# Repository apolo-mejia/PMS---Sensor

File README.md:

# PMS_Sensor
Power manage System for Microcontrolles ans sensors, in the scope of Syracuza proyect. 
Features:
- Automatic connetion/disconnection, from Li-ION battery protection,
- Automatic disconnection a battery when a external alimentation is provided,
- Compatible with Energy Harvest, <br>

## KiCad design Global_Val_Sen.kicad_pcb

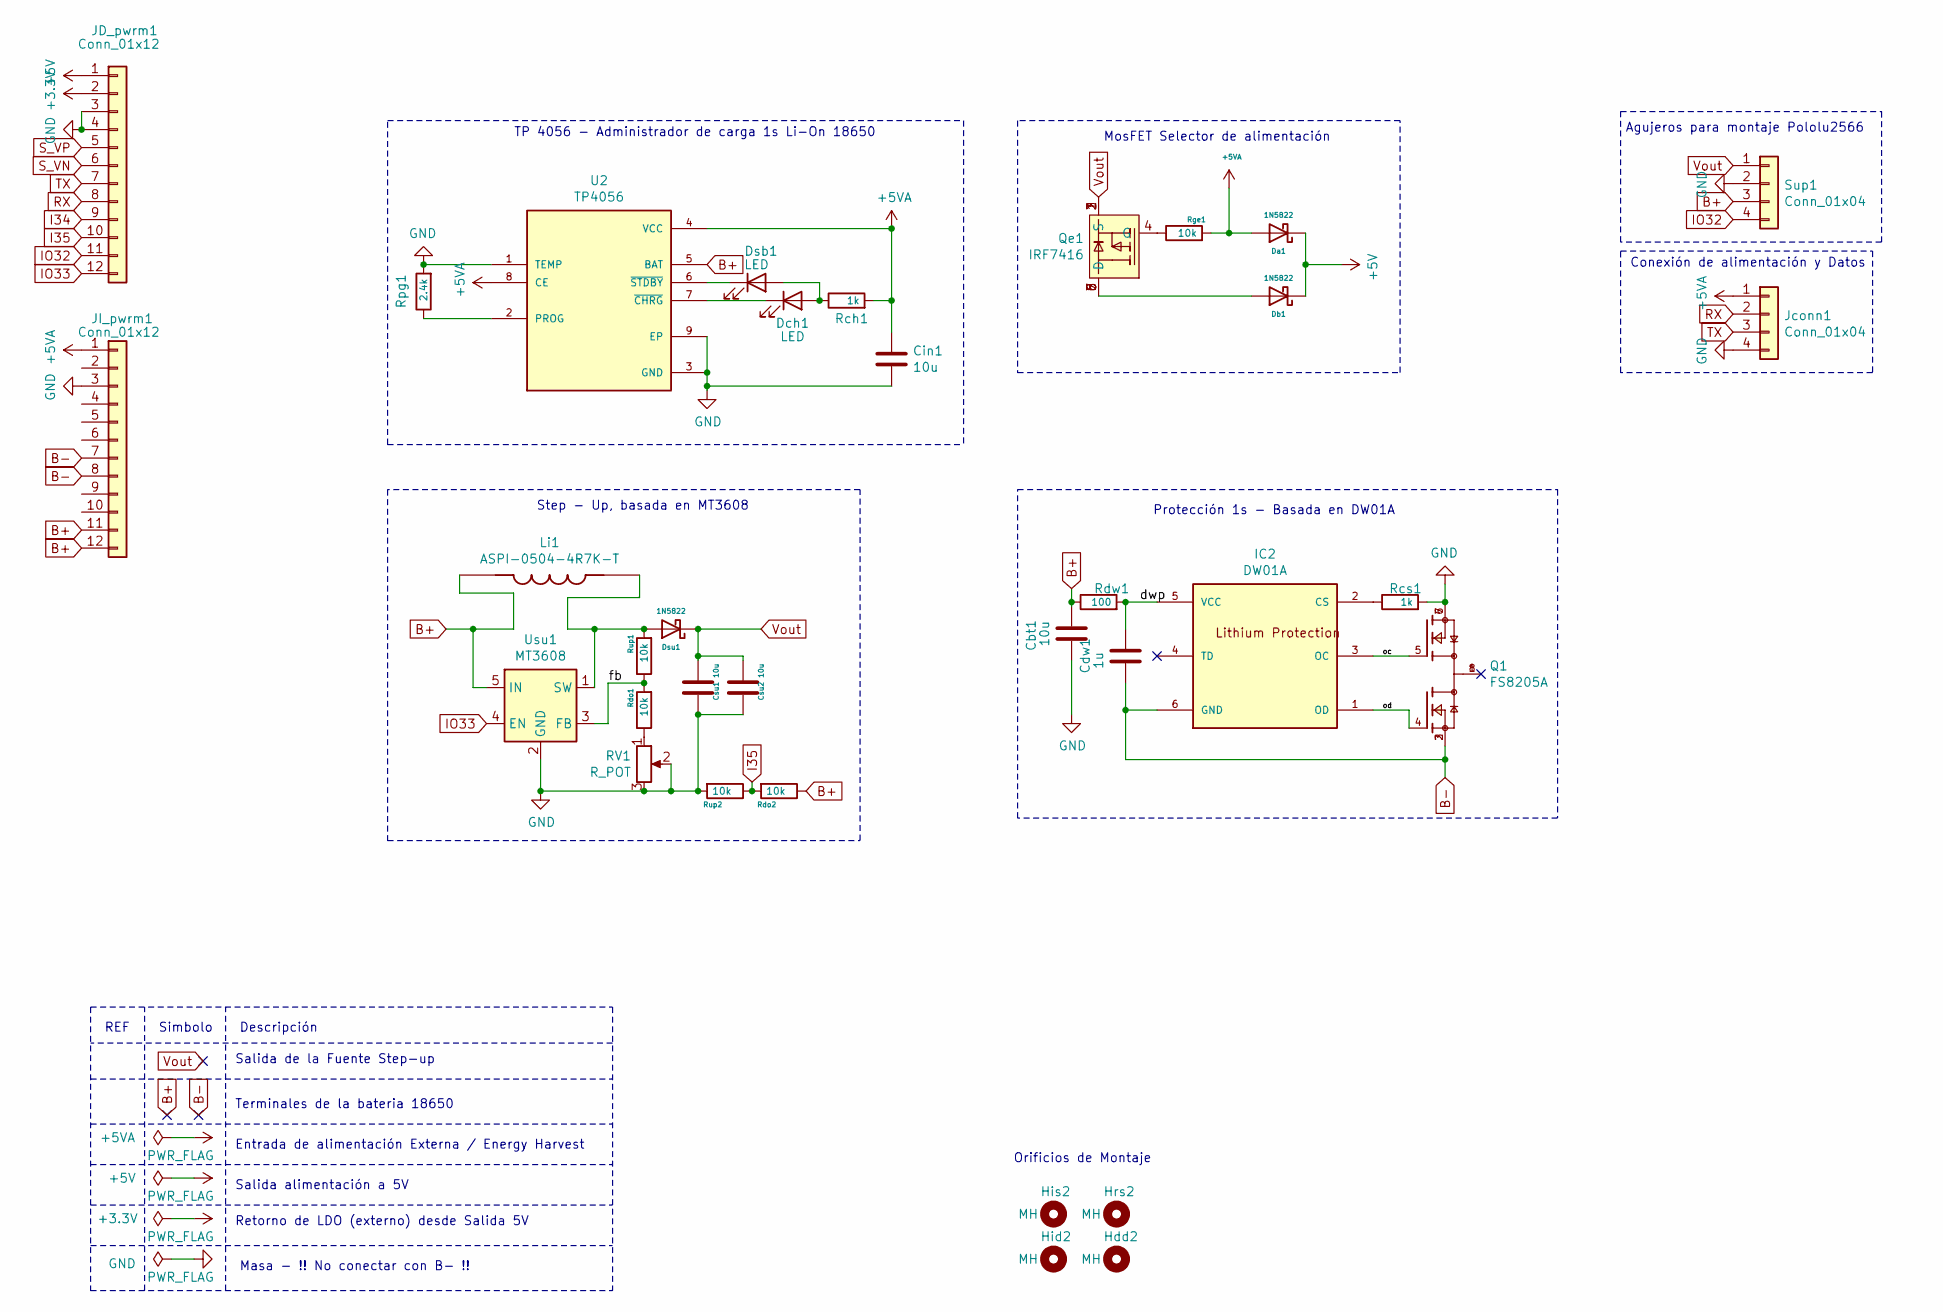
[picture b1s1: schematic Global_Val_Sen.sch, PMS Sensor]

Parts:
Cbt1: 10u; CP_EIA-3216-10_Kemet-I_Pad1.58x1.35mm_HandSolder
Cdw1: 1u; CP_EIA-3216-10_Kemet-I_Pad1.58x1.35mm_HandSolder
Cin1: 10u; CP_EIA-3216-10_Kemet-I_Pad1.58x1.35mm_HandSolder
Csu1, Csu2: 10u; CP_EIA-3216-10_Kemet-I_Pad1.58x1.35mm_HandSolder
Da1: 1N5822; D_SMA
Db1: 1N5822; D_SMA
Dch1: LED; LED_1206_3216Metric_Castellated
Dsb1: LED; LED_1206_3216Metric_Castellated
Dsu1: 1N5822; D_SMA
Hdd2: MH; MountingHole_2.2mm_M2_DIN965
Hid2: MH; MountingHole_2.2mm_M2_DIN965
His2: MH; MountingHole_2.2mm_M2_DIN965
Hrs2: MH; MountingHole_2.2mm_M2_DIN965
IC2: DW01A; SOT-23-6_Handsoldering
JD_pwrm1: Conn_01x12; PinSocket_1x12_P2.00mm_Vertical
JI_pwrm1: Conn_01x12; PinSocket_1x12_P2.00mm_Vertical
Jconn1: Conn_01x04; PinHeader_1x04_P2.00mm_Vertical
Li1: ASPI-0504-4R7K-T; IND_ASPI-0504-4R7K-T; PARTREV 06.24.13
Q1: FS8205A; SOP65P640X120-8N; PARTREV 1.7
Qe1: IRF7416; SO-8_3.9x4.9mm_P1.27mm
RV1: R_POT; Potentiometer_Bourns_TC33X_Vertical
Rch1: 1k; R_1206_3216Metric_Pad1.30x1.75mm_HandSolder
Rcs1: 1k; R_1206_3216Metric_Pad1.30x1.75mm_HandSolder
Rdo1, Rdo2: 10k; R_1206_3216Metric_Pad1.30x1.75mm_HandSolder
Rdw1: 100; R_1206_3216Metric_Pad1.30x1.75mm_HandSolder
Rge1: 10k; R_1206_3216Metric_Pad1.30x1.75mm_HandSolder
Rpg1: 2.4k; R_1206_3216Metric_Pad1.30x1.75mm_HandSolder
Rup1, Rup2: 10k; R_1206_3216Metric_Pad1.30x1.75mm_HandSolder
Sup1: Conn_01x04; PinSocket_1x04_P2.54mm_Vertical
U2: TP4056; SOP127P600X175-9N
Usu1: MT3608; SOT-23-6

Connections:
+3V3: JD_pwrm1.2
+5V: Da1.1 (K), Db1.1 (K), JD_pwrm1.1
+5VA: Cin1.1, Da1.2 (A), JI_pwrm1.1, Jconn1.1, Rch1.2, Rge1.2, U2.4 (VCC), U2.8 (CE)
/dwp: Cdw1.1, IC2.5 (VCC), Rdw1.2
/fb: Rdo1.2, Rup1.1, Usu1.3 (FB)
/oc: IC2.3 (OC), Q1.5
/od: IC2.1 (OD), Q1.4
B+: Cbt1.1, JI_pwrm1.11, JI_pwrm1.12, Li1.1, Rdo2.1, Rdw1.1, Sup1.3, U2.5 (BAT), Usu1.5 (IN)
B-: Cdw1.2, IC2.6 (GND), JI_pwrm1.7, JI_pwrm1.8, Q1.2, Q1.3
I34: JD_pwrm1.9
I35: JD_pwrm1.10, Rdo2.2, Rup2.1
IO32: JD_pwrm1.11, Sup1.4
IO33: JD_pwrm1.12, Usu1.4 (EN)
unnamed: Db1.2 (A), Qe1.5 (D), Qe1.6 (D), Qe1.7 (D), Qe1.8 (D)
unnamed: Dch1.1 (K), U2.7 (~CHRG)
unnamed: Dch1.2 (A), Dsb1.2 (A), Rch1.1
unnamed: Dsb1.1 (K), U2.6 (~STDBY)
unnamed: Dsu1.2 (A), Li1.2, Rup1.2, Usu1.1 (SW)
unnamed: IC2.2 (CS), Rcs1.1
unnamed: Q1.1, Q1.8
unnamed: Qe1.4 (G), Rge1.1
unnamed: RV1.1, Rdo1.1
unnamed: Rpg1.1, U2.2 (PROG)
RX: JD_pwrm1.8, Jconn1.2
S_VN: JD_pwrm1.6
S_VP: JD_pwrm1.5
TX: JD_pwrm1.7, Jconn1.3
Vout: Csu1.1, Csu2.1, Dsu1.1 (K), Qe1.1 (S), Qe1.2 (S), Qe1.3 (S), Sup1.1

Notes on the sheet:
MosFET Selector de alimentación
Orificios de Montaje
Entrada de alimentación Externa / Energy Harvest
Salida alimentación a 5V
Retorno de LDO (externo) desde Salida 5V
TP 4056 - Administrador de carga 1s Li-On 18650
Step - Up, basada en MT3608
Protección 1s - Basada en DW01A
Agujeros para montaje Pololu2566
Terminales de la bateria 18650
Salida de la Fuente Step-up
Masa - !! No conectar con B- !!
REF
Simbolo
Descripción
Conexión de alimentación y Datos

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
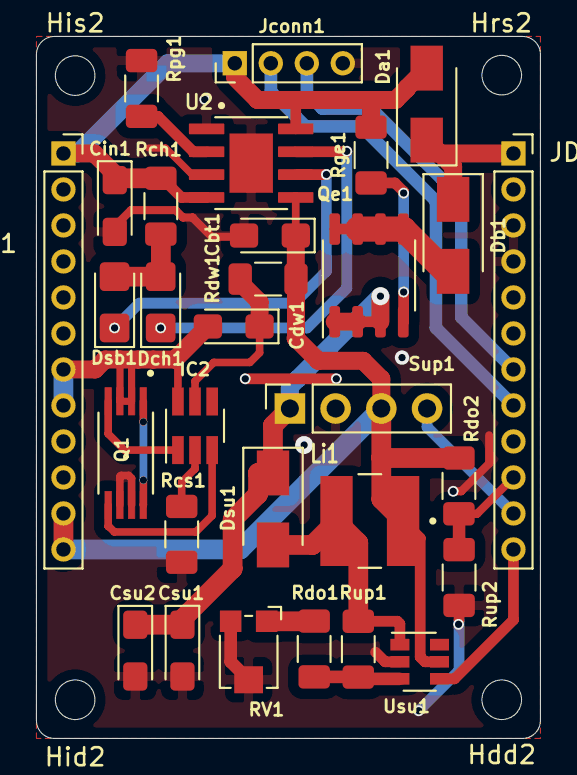
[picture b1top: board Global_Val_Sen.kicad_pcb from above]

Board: 2 copper layers, 28.0 x 39.0 mm, 34 parts (0 on the bottom side), 25 nets.

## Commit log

2022-11-27 Inicial Commit
